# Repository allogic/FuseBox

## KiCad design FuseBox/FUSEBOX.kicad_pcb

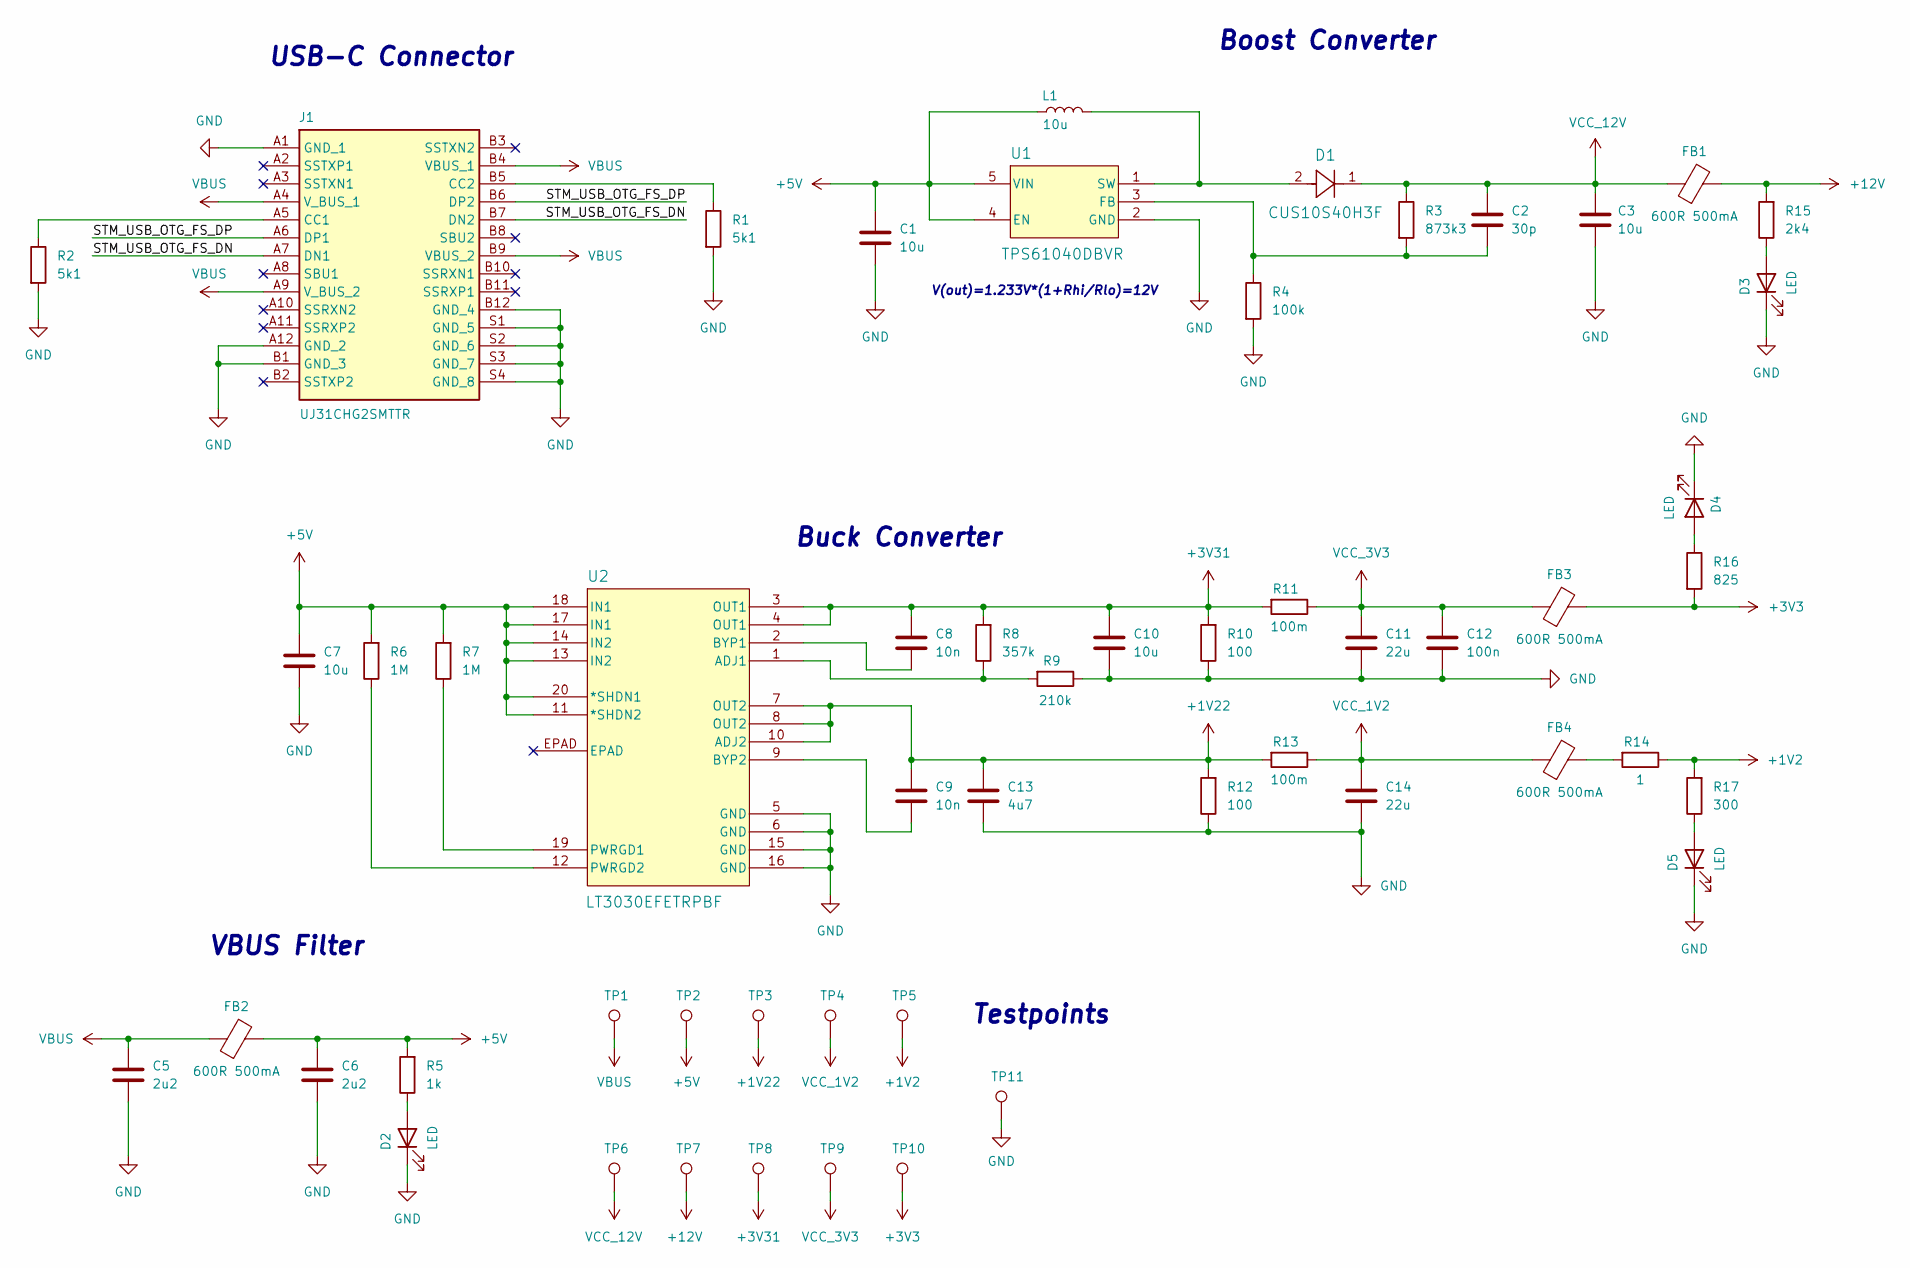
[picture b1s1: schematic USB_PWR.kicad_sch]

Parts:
C1, C3, C7, C10: 10u; C_0603_1608Metric_Pad1.08x0.95mm_HandSolder
C2: 30p; C_0603_1608Metric_Pad1.08x0.95mm_HandSolder
C5, C6: 2u2; C_0603_1608Metric_Pad1.08x0.95mm_HandSolder
C8, C9: 10n; C_0603_1608Metric_Pad1.08x0.95mm_HandSolder
C11, C14: 22u; C_0603_1608Metric_Pad1.08x0.95mm_HandSolder
C12: 100n; C_0603_1608Metric_Pad1.08x0.95mm_HandSolder
C13: 4u7; C_0603_1608Metric_Pad1.08x0.95mm_HandSolder
D1: CUS10S40H3F
D2, D3, D4, D5: LED; LED_0603_1608Metric
FB1, FB2, FB3, FB4: 600R 500mA; L_0603_1608Metric_Pad1.05x0.95mm_HandSolder
J1: UJ31CHG2SMTTR; Manufacturer_Part_Number UJ31-CH-G2-SMT-TR; Mouser Part Number 490-UJ31-CH-G2SMT-TR
L1: 10u; L_0603_1608Metric_Pad1.05x0.95mm_HandSolder
R1, R2: 5k1; R_0603_1608Metric_Pad0.98x0.95mm_HandSolder
R3: 873k3; R_0603_1608Metric_Pad0.98x0.95mm_HandSolder
R4: 100k; R_0603_1608Metric_Pad0.98x0.95mm_HandSolder
R5: 1k; R_0603_1608Metric_Pad0.98x0.95mm_HandSolder
R6, R7: 1M; R_0603_1608Metric_Pad0.98x0.95mm_HandSolder
R8: 357k; R_0603_1608Metric_Pad0.98x0.95mm_HandSolder
R9: 210k; R_0603_1608Metric_Pad0.98x0.95mm_HandSolder
R10, R12: 100; R_0603_1608Metric_Pad0.98x0.95mm_HandSolder
R11, R13: 100m; R_0603_1608Metric_Pad0.98x0.95mm_HandSolder
R14: 1; R_0603_1608Metric_Pad0.98x0.95mm_HandSolder
R15: 2k4; R_0603_1608Metric_Pad0.98x0.95mm_HandSolder
R16: 825; R_0603_1608Metric_Pad0.98x0.95mm_HandSolder
R17: 300; R_0603_1608Metric_Pad0.98x0.95mm_HandSolder
TP1, TP2, TP3, TP4, TP5, TP6, TP7, TP8, TP9, TP10, TP11: TestPoint; TestPoint_Pad_D3.0mm
U1: TPS61040DBVR
U2: LT3030EFETRPBF; LT8302ES8ETRPBF

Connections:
+1V2: R14.1, R17.2, TP5.1; also elsewhere on the board
+1V22: C9.1, C13.1, R12.2, R13.2, TP3.1, U2.7 (OUT2), U2.8 (OUT2), U2.10 (ADJ2)
+3V3: FB3.2, R16.2, TP10.1; also elsewhere on the board
+3V31: C8.1, C10.1, R8.2, R10.2, R11.2, TP8.1, U2.3 (OUT1), U2.4 (OUT1)
+5V: C1.1, C6.1, C7.1, FB2.2, L1.1, R5.2, R6.2, R7.2, TP2.1, U1.4 (EN), U1.5 (VIN), U2.11 (*SHDN2), U2.13 (IN2), U2.14 (IN2), U2.17 (IN1), U2.18 (IN1), U2.20 (*SHDN1)
+12V: FB1.2, R15.2, TP7.1
/USB_PWR/STM_USB_OTG_FS_DN: J1.A7 (DN1), J1.B7 (DN2)
/USB_PWR/STM_USB_OTG_FS_DP: J1.A6 (DP1), J1.B6 (DP2)
GND: C1.2, C3.2, C5.2, C6.2, C7.2, C10.2, C11.2, C12.2, C13.2, C14.2, D2.1 (K), D3.1 (K), D4.1 (K), D5.1 (K), J1.A1 (GND_1), J1.A12 (GND_2), J1.B1 (GND_3), J1.B12 (GND_4), J1.S1 (GND_5), J1.S2 (GND_6), J1.S3 (GND_7), J1.S4 (GND_8), R1.2, R2.2, R4.2, R9.1, R10.1, R12.1, TP11.1, U1.2 (GND), U2.5 (GND), U2.6 (GND), U2.15 (GND), U2.16 (GND); also elsewhere on the board
unnamed: D2.2 (A), R5.1
unnamed: D3.2 (A), R15.1
unnamed: D4.2 (A), R16.1
unnamed: D5.2 (A), R17.1
unnamed: FB4.2, R14.2
unnamed: J1.A5 (CC1), R2.1
unnamed: J1.B5 (CC2), R1.1
unnamed: C2.2, R3.2, R4.1, U1.3 (FB)
unnamed: D1.2, L1.2, U1.1 (SW)
unnamed: R8.1, R9.2, U2.1 (ADJ1)
unnamed: C8.2, U2.2 (BYP1)
unnamed: C9.2, U2.9 (BYP2)
unnamed: R7.1, U2.19 (PWRGD1)
unnamed: R6.1, U2.12 (PWRGD2)
VBUS: C5.1, FB2.1, J1.A4 (V_BUS_1), J1.A9 (V_BUS_2), J1.B4 (VBUS_1), J1.B9 (VBUS_2), TP1.1
VCC_1V2: C14.1, FB4.1, R13.1, TP4.1
VCC_3V3: C11.1, C12.1, FB3.1, R11.1, TP9.1
VCC_12V: C2.1, C3.1, D1.1, FB1.1, R3.1, TP6.1

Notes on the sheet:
Boost Converter
VBUS Filter
Buck Converter
V(out)=1.233V*(1+Rhi/Rlo)=12V
USB-C Connector
Testpoints

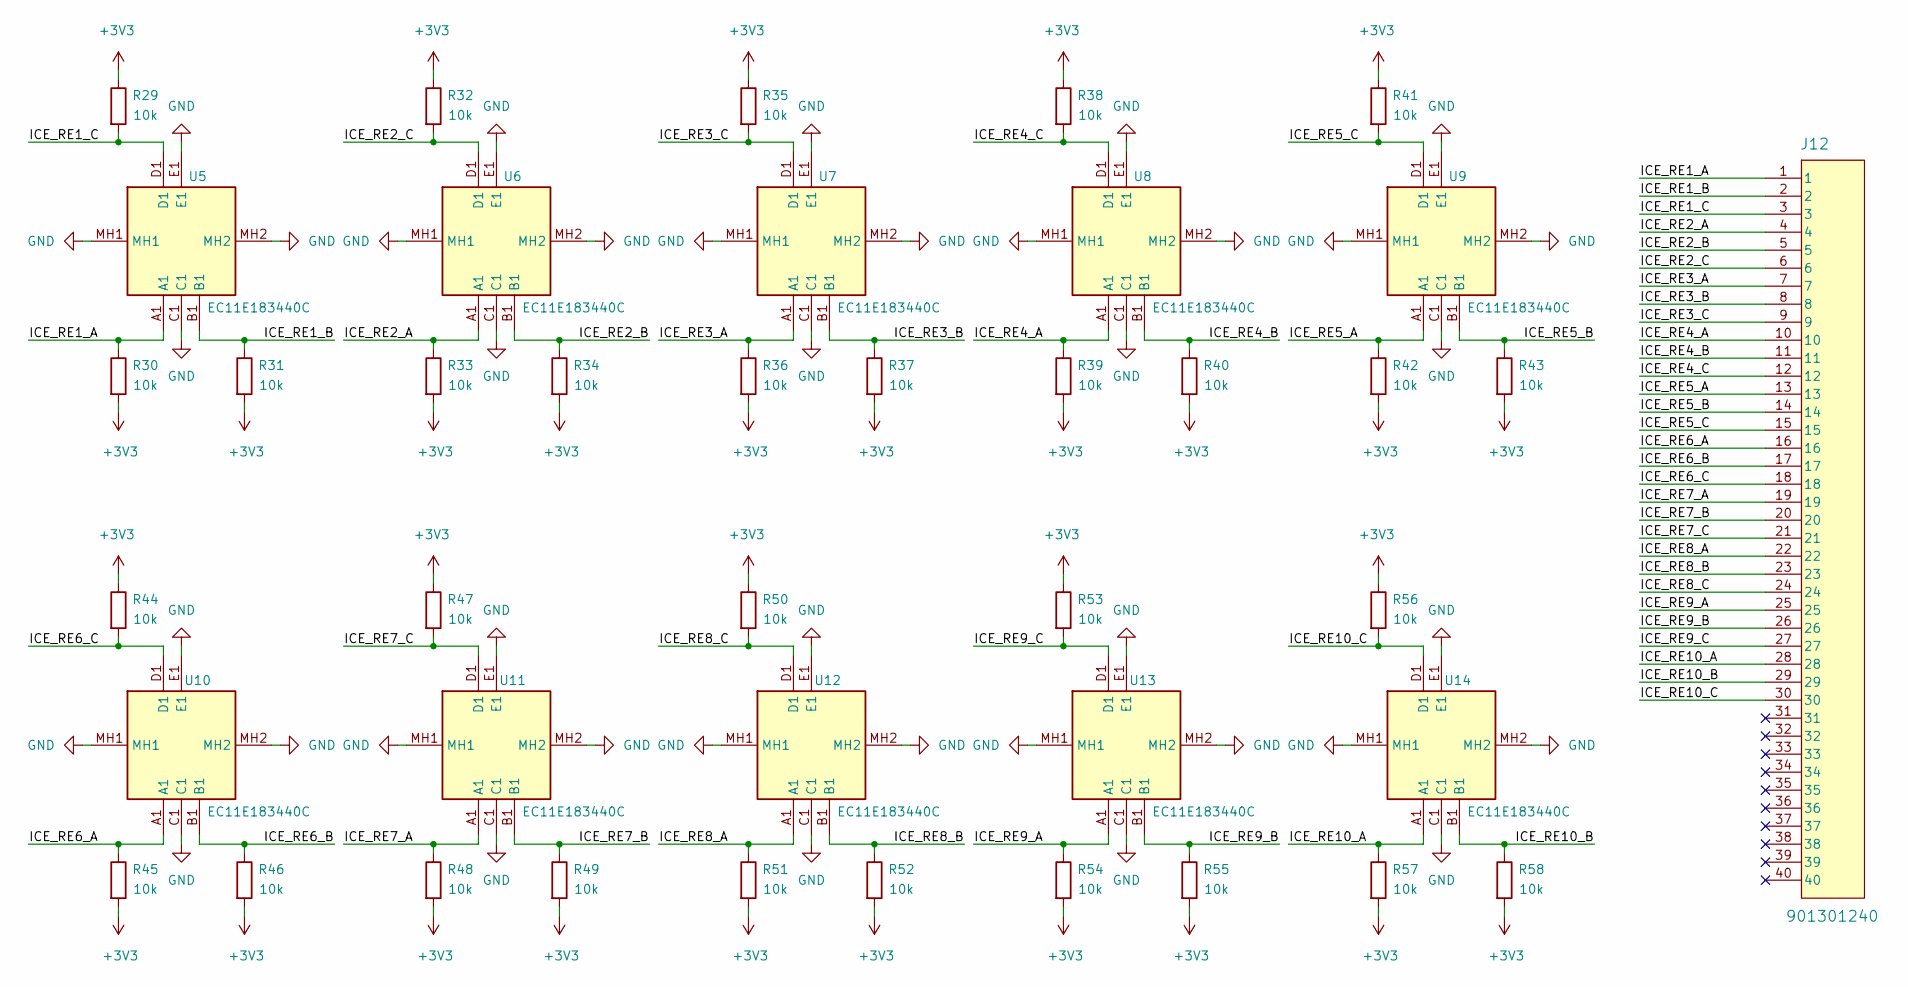
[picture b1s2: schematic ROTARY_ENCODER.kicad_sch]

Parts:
J12: 901301240
R29, R30, R31, R32, R33, R34, R35, R36, R37, R38, R39, R40, R41, R42, R43, R44, R45, R46, R47, R48, R49, R50, R51, R52, R53, R54, R55, R56, R57, R58: 10k; R_0603_1608Metric_Pad0.98x0.95mm_HandSolder
U5, U6, U7, U8, U9, U10, U11, U12, U13, U14: EC11E183440C; Manufacturer_Part_Number EC11E183440C; Mouser Part Number 688-EC11E183440C

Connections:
+3V3: R29.1, R30.2, R31.2, R32.1, R33.2, R34.2, R35.1, R36.2, R37.2, R38.1, R39.2, R40.2, R41.1, R42.2, R43.2, R44.1, R45.2, R46.2, R47.1, R48.2, R49.2, R50.1, R51.2, R52.2, R53.1, R54.2, R55.2, R56.1, R57.2, R58.2; also elsewhere on the board
/ROTARY_ENCODER/ICE_RE1_A: J12.1, R30.1, U5.A1
/ROTARY_ENCODER/ICE_RE1_B: J12.2, R31.1, U5.B1
/ROTARY_ENCODER/ICE_RE1_C: J12.3, R29.2, U5.D1
/ROTARY_ENCODER/ICE_RE2_A: J12.4, R33.1, U6.A1
/ROTARY_ENCODER/ICE_RE2_B: J12.5, R34.1, U6.B1
/ROTARY_ENCODER/ICE_RE2_C: J12.6, R32.2, U6.D1
/ROTARY_ENCODER/ICE_RE3_A: J12.7, R36.1, U7.A1
/ROTARY_ENCODER/ICE_RE3_B: J12.8, R37.1, U7.B1
/ROTARY_ENCODER/ICE_RE3_C: J12.9, R35.2, U7.D1
/ROTARY_ENCODER/ICE_RE4_A: J12.10, R39.1, U8.A1
/ROTARY_ENCODER/ICE_RE4_B: J12.11, R40.1, U8.B1
/ROTARY_ENCODER/ICE_RE4_C: J12.12, R38.2, U8.D1
/ROTARY_ENCODER/ICE_RE5_A: J12.13, R42.1, U9.A1
/ROTARY_ENCODER/ICE_RE5_B: J12.14, R43.1, U9.B1
/ROTARY_ENCODER/ICE_RE5_C: J12.15, R41.2, U9.D1
/ROTARY_ENCODER/ICE_RE6_A: J12.16, R45.1, U10.A1
/ROTARY_ENCODER/ICE_RE6_B: J12.17, R46.1, U10.B1
/ROTARY_ENCODER/ICE_RE6_C: J12.18, R44.2, U10.D1
/ROTARY_ENCODER/ICE_RE7_A: J12.19, R48.1, U11.A1
/ROTARY_ENCODER/ICE_RE7_B: J12.20, R49.1, U11.B1
/ROTARY_ENCODER/ICE_RE7_C: J12.21, R47.2, U11.D1
/ROTARY_ENCODER/ICE_RE8_A: J12.22, R51.1, U12.A1
/ROTARY_ENCODER/ICE_RE8_B: J12.23, R52.1, U12.B1
/ROTARY_ENCODER/ICE_RE8_C: J12.24, R50.2, U12.D1
/ROTARY_ENCODER/ICE_RE9_A: J12.25, R54.1, U13.A1
/ROTARY_ENCODER/ICE_RE9_B: J12.26, R55.1, U13.B1
/ROTARY_ENCODER/ICE_RE9_C: J12.27, R53.2, U13.D1
/ROTARY_ENCODER/ICE_RE10_A: J12.28, R57.1, U14.A1
/ROTARY_ENCODER/ICE_RE10_B: J12.29, R58.1, U14.B1
/ROTARY_ENCODER/ICE_RE10_C: J12.30, R56.2, U14.D1
GND: U5.C1, U5.E1, U5.MH1, U5.MH2, U6.C1, U6.E1, U6.MH1, U6.MH2, U7.C1, U7.E1, U7.MH1, U7.MH2, U8.C1, U8.E1, U8.MH1, U8.MH2, U9.C1, U9.E1, U9.MH1, U9.MH2, U10.C1, U10.E1, U10.MH1, U10.MH2, U11.C1, U11.E1, U11.MH1, U11.MH2, U12.C1, U12.E1, U12.MH1, U12.MH2, U13.C1, U13.E1, U13.MH1, U13.MH2, U14.C1, U14.E1, U14.MH1, U14.MH2; also elsewhere on the board

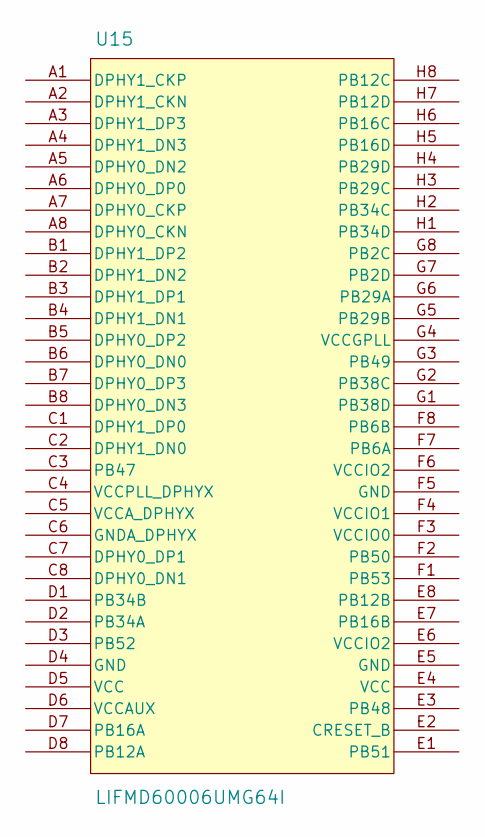
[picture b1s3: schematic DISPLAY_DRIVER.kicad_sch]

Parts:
U15: LIFMD60006UMG64I

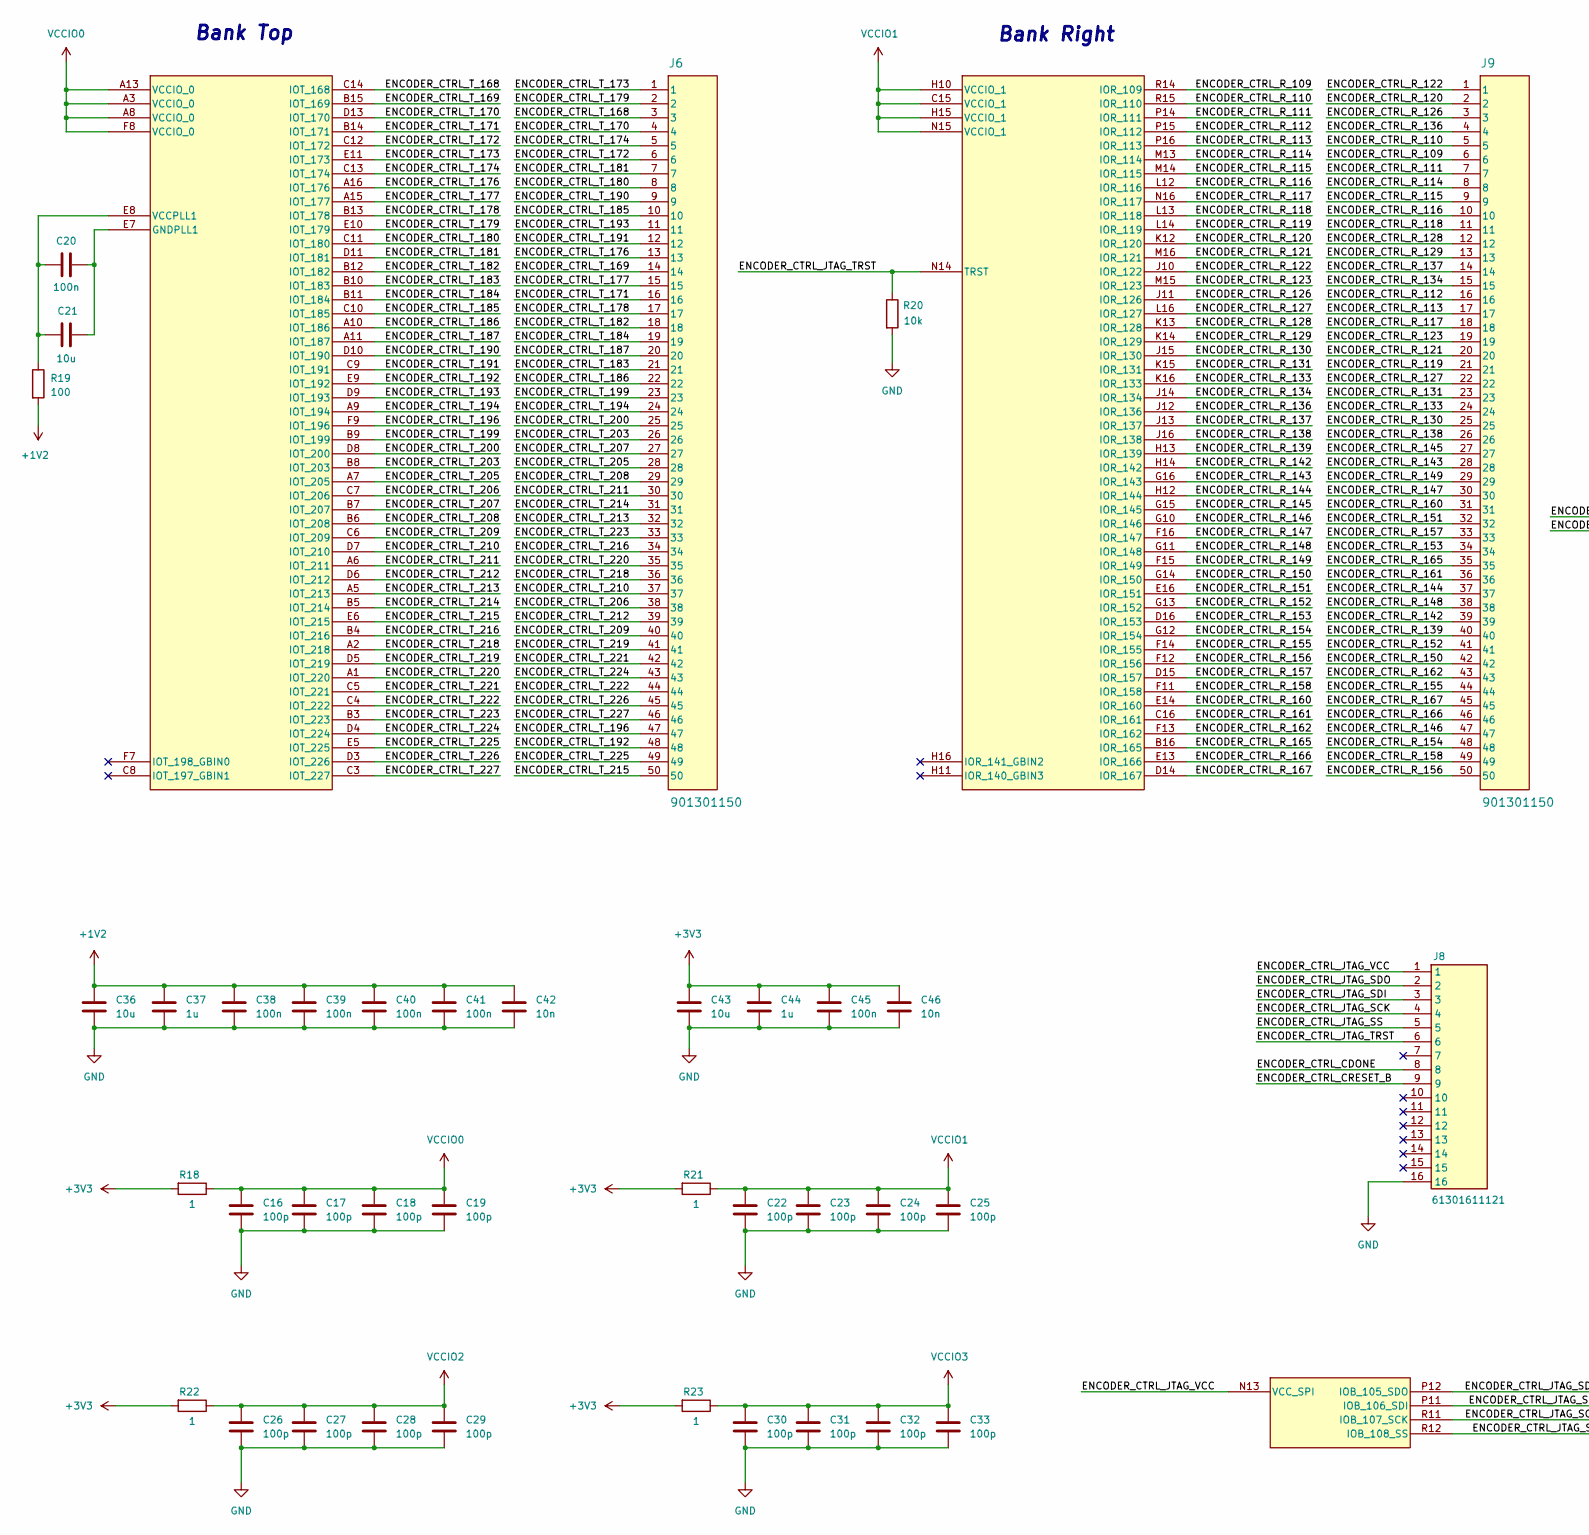
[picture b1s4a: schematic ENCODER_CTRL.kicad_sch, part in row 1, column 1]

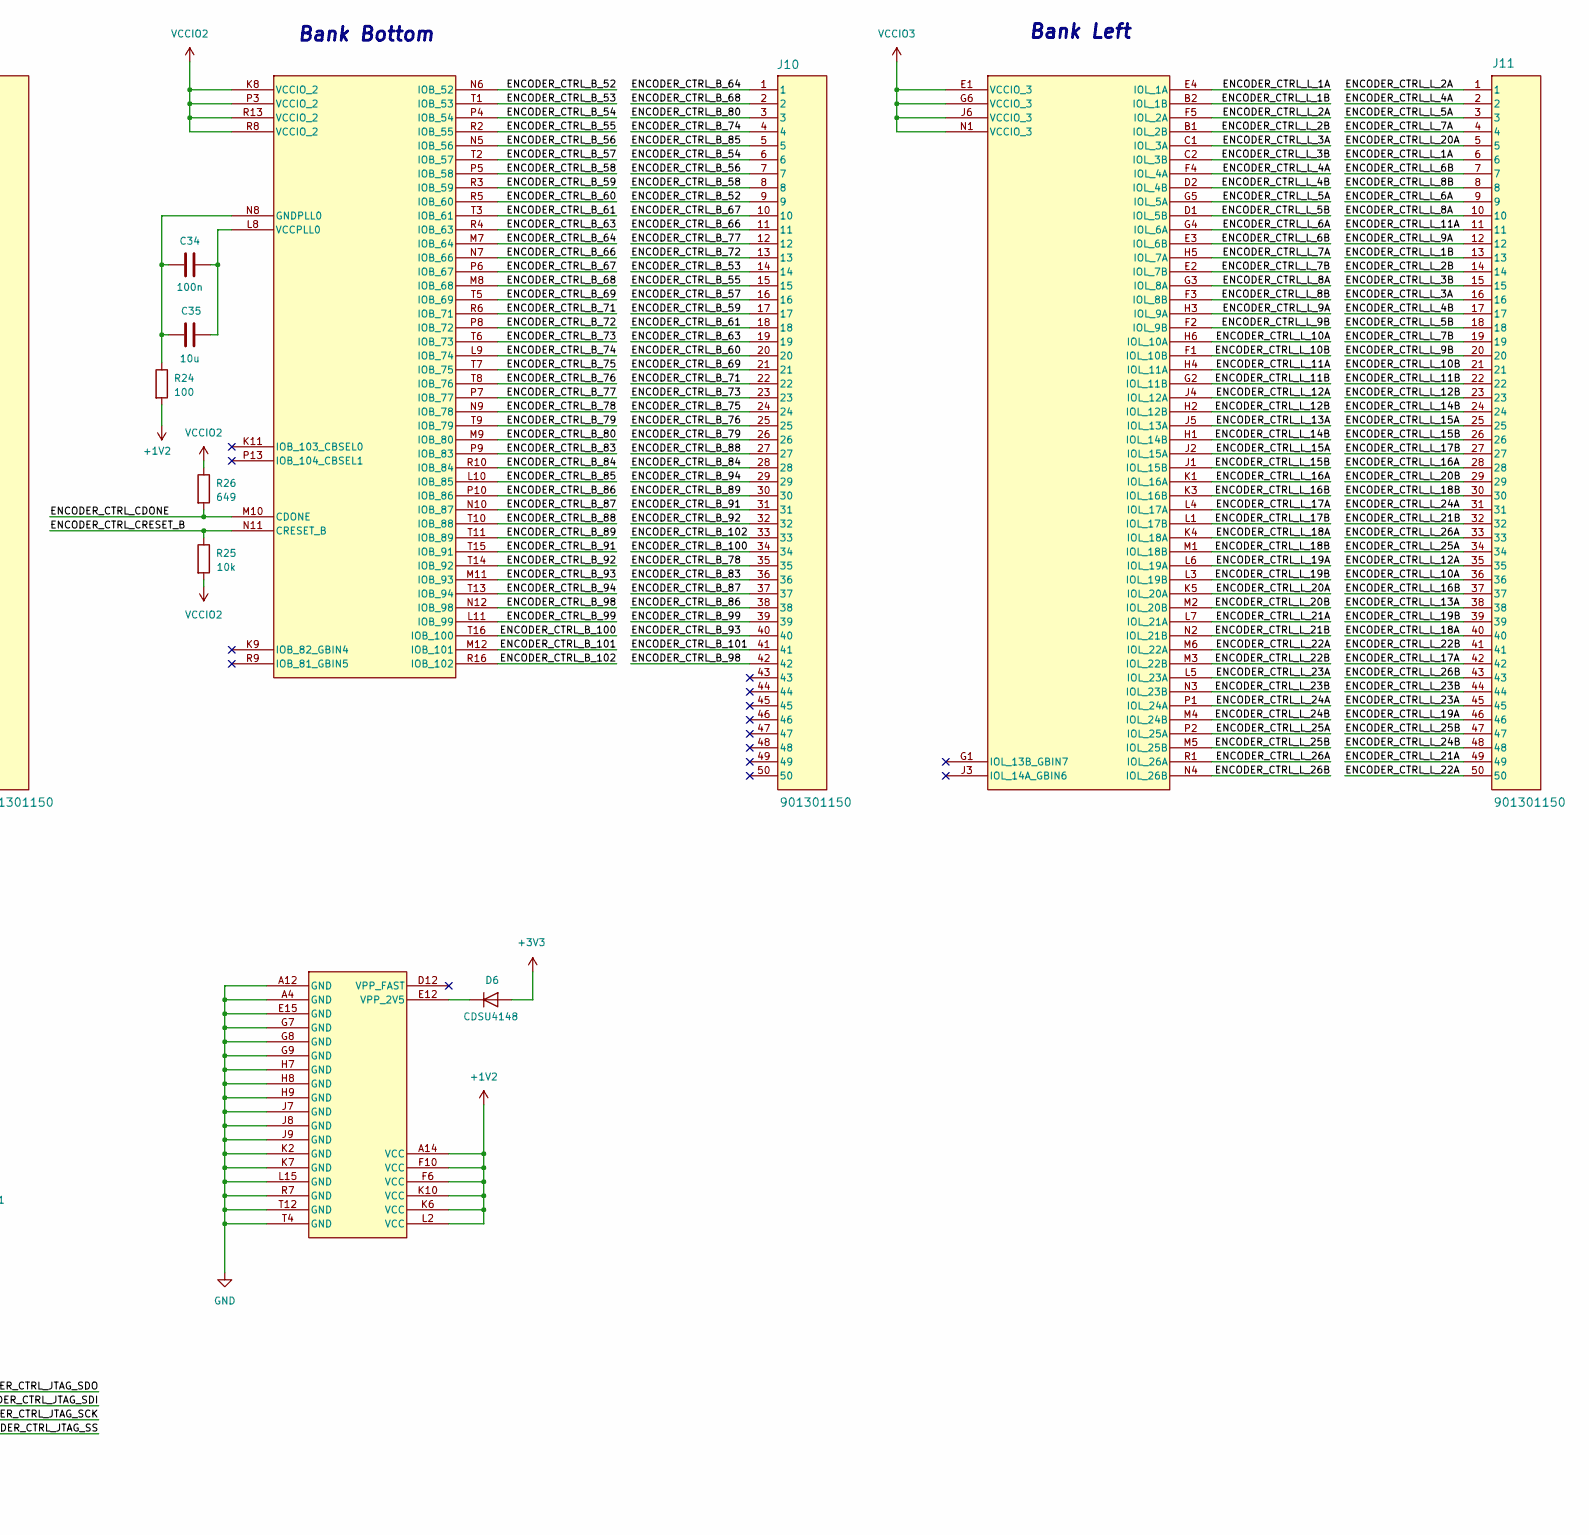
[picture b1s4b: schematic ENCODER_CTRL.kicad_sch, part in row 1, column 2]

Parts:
C16, C17, C18, C19, C22, C23, C24, C25, C26, C27, C28, C29, C30, C31, C32, C33: 100p; C_0603_1608Metric_Pad1.08x0.95mm_HandSolder
C20, C34, C38, C39, C40, C41, C45: 100n; C_0603_1608Metric_Pad1.08x0.95mm_HandSolder
C21, C35, C36, C43: 10u; C_0603_1608Metric_Pad1.08x0.95mm_HandSolder
C37, C44: 1u; C_0603_1608Metric_Pad1.08x0.95mm_HandSolder
C42, C46: 10n; C_0603_1608Metric_Pad1.08x0.95mm_HandSolder
D6: CDSU4148; D_0603_1608Metric_Pad1.05x0.95mm_HandSolder
J6, J9, J10, J11: 901301150
J8: 61301611121; Manufacturer_Part_Number 61301611121; Mouser Part Number 710-61301611121
R18, R21, R22, R23: 1; R_0603_1608Metric_Pad0.98x0.95mm_HandSolder
R19, R24: 100; R_0603_1608Metric_Pad0.98x0.95mm_HandSolder
R20, R25: 10k; R_0603_1608Metric_Pad0.98x0.95mm_HandSolder
R26: 649; R_0603_1608Metric_Pad0.98x0.95mm_HandSolder
U4: ICE40HX8KCT256

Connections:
+1V2: C36.1, C37.1, C38.1, C39.1, C40.1, C41.1, C42.1, R19.2, R24.2, U4.A14 (VCC), U4.F6 (VCC), U4.F10 (VCC), U4.K6 (VCC), U4.K10 (VCC), U4.L2 (VCC); also elsewhere on the board
+3V3: C43.1, C44.1, C45.1, C46.1, D6.2 (A), R18.2, R21.2, R22.2, R23.2; also elsewhere on the board
/ENCODER_CTRL/ENCODER_CTRL_B_52: J10.9, U4.N6 (IOB_52)
/ENCODER_CTRL/ENCODER_CTRL_B_53: J10.14, U4.T1 (IOB_53)
/ENCODER_CTRL/ENCODER_CTRL_B_54: J10.6, U4.P4 (IOB_54)
/ENCODER_CTRL/ENCODER_CTRL_B_55: J10.15, U4.R2 (IOB_55)
/ENCODER_CTRL/ENCODER_CTRL_B_56: J10.7, U4.N5 (IOB_56)
/ENCODER_CTRL/ENCODER_CTRL_B_57: J10.16, U4.T2 (IOB_57)
/ENCODER_CTRL/ENCODER_CTRL_B_58: J10.8, U4.P5 (IOB_58)
/ENCODER_CTRL/ENCODER_CTRL_B_59: J10.17, U4.R3 (IOB_59)
/ENCODER_CTRL/ENCODER_CTRL_B_60: J10.20, U4.R5 (IOB_60)
/ENCODER_CTRL/ENCODER_CTRL_B_61: J10.18, U4.T3 (IOB_61)
/ENCODER_CTRL/ENCODER_CTRL_B_63: J10.19, U4.R4 (IOB_63)
/ENCODER_CTRL/ENCODER_CTRL_B_64: J10.1, U4.M7 (IOB_64)
/ENCODER_CTRL/ENCODER_CTRL_B_66: J10.11, U4.N7 (IOB_66)
/ENCODER_CTRL/ENCODER_CTRL_B_67: J10.10, U4.P6 (IOB_67)
/ENCODER_CTRL/ENCODER_CTRL_B_68: J10.2, U4.M8 (IOB_68)
/ENCODER_CTRL/ENCODER_CTRL_B_69: J10.21, U4.T5 (IOB_69)
/ENCODER_CTRL/ENCODER_CTRL_B_71: J10.22, U4.R6 (IOB_71)
/ENCODER_CTRL/ENCODER_CTRL_B_72: J10.13, U4.P8 (IOB_72)
/ENCODER_CTRL/ENCODER_CTRL_B_73: J10.23, U4.T6 (IOB_73)
/ENCODER_CTRL/ENCODER_CTRL_B_74: J10.4, U4.L9 (IOB_74)
/ENCODER_CTRL/ENCODER_CTRL_B_75: J10.24, U4.T7 (IOB_75)
/ENCODER_CTRL/ENCODER_CTRL_B_76: J10.25, U4.T8 (IOB_76)
/ENCODER_CTRL/ENCODER_CTRL_B_77: J10.12, U4.P7 (IOB_77)
/ENCODER_CTRL/ENCODER_CTRL_B_78: J10.35, U4.N9 (IOB_78)
/ENCODER_CTRL/ENCODER_CTRL_B_79: J10.26, U4.T9 (IOB_79)
/ENCODER_CTRL/ENCODER_CTRL_B_80: J10.3, U4.M9 (IOB_80)
/ENCODER_CTRL/ENCODER_CTRL_B_83: J10.36, U4.P9 (IOB_83)
/ENCODER_CTRL/ENCODER_CTRL_B_84: J10.28, U4.R10 (IOB_84)
/ENCODER_CTRL/ENCODER_CTRL_B_85: J10.5, U4.L10 (IOB_85)
/ENCODER_CTRL/ENCODER_CTRL_B_86: J10.38, U4.P10 (IOB_86)
/ENCODER_CTRL/ENCODER_CTRL_B_87: J10.37, U4.N10 (IOB_87)
/ENCODER_CTRL/ENCODER_CTRL_B_88: J10.27, U4.T10 (IOB_88)
/ENCODER_CTRL/ENCODER_CTRL_B_89: J10.30, U4.T11 (IOB_89)
/ENCODER_CTRL/ENCODER_CTRL_B_91: J10.31, U4.T15 (IOB_91)
/ENCODER_CTRL/ENCODER_CTRL_B_92: J10.32, U4.T14 (IOB_92)
/ENCODER_CTRL/ENCODER_CTRL_B_93: J10.40, U4.M11 (IOB_93)
/ENCODER_CTRL/ENCODER_CTRL_B_94: J10.29, U4.T13 (IOB_94)
/ENCODER_CTRL/ENCODER_CTRL_B_98: J10.42, U4.N12 (IOB_98)
/ENCODER_CTRL/ENCODER_CTRL_B_99: J10.39, U4.L11 (IOB_99)
/ENCODER_CTRL/ENCODER_CTRL_B_100: J10.34, U4.T16 (IOB_100)
/ENCODER_CTRL/ENCODER_CTRL_B_101: J10.41, U4.M12 (IOB_101)
/ENCODER_CTRL/ENCODER_CTRL_B_102: J10.33, U4.R16 (IOB_102)
/ENCODER_CTRL/ENCODER_CTRL_CDONE: J8.8, R26.2, U4.M10 (CDONE)
/ENCODER_CTRL/ENCODER_CTRL_CRESET_B: J8.9, R25.1, U4.N11 (CRESET_B)
/ENCODER_CTRL/ENCODER_CTRL_JTAG_SCK: J8.4, U4.R11 (IOB_107_SCK)
/ENCODER_CTRL/ENCODER_CTRL_JTAG_SDI: J8.3, U4.P11 (IOB_106_SDI)
/ENCODER_CTRL/ENCODER_CTRL_JTAG_SDO: J8.2, U4.P12 (IOB_105_SDO)
/ENCODER_CTRL/ENCODER_CTRL_JTAG_SS: J8.5, U4.R12 (IOB_108_SS)
/ENCODER_CTRL/ENCODER_CTRL_JTAG_TRST: J8.6, R20.1, U4.N14 (TRST)
/ENCODER_CTRL/ENCODER_CTRL_JTAG_VCC: J8.1, U4.N13 (VCC_SPI)
/ENCODER_CTRL/ENCODER_CTRL_L_1A: J11.6, U4.E4 (IOL_1A)
/ENCODER_CTRL/ENCODER_CTRL_L_1B: J11.13, U4.B2 (IOL_1B)
/ENCODER_CTRL/ENCODER_CTRL_L_2A: J11.1, U4.F5 (IOL_2A)
/ENCODER_CTRL/ENCODER_CTRL_L_2B: J11.14, U4.B1 (IOL_2B)
/ENCODER_CTRL/ENCODER_CTRL_L_3A: J11.16, U4.C1 (IOL_3A)
/ENCODER_CTRL/ENCODER_CTRL_L_3B: J11.15, U4.C2 (IOL_3B)
/ENCODER_CTRL/ENCODER_CTRL_L_4A: J11.2, U4.F4 (IOL_4A)
/ENCODER_CTRL/ENCODER_CTRL_L_4B: J11.17, U4.D2 (IOL_4B)
/ENCODER_CTRL/ENCODER_CTRL_L_5A: J11.3, U4.G5 (IOL_5A)
/ENCODER_CTRL/ENCODER_CTRL_L_5B: J11.18, U4.D1 (IOL_5B)
/ENCODER_CTRL/ENCODER_CTRL_L_6A: J11.9, U4.G4 (IOL_6A)
/ENCODER_CTRL/ENCODER_CTRL_L_6B: J11.7, U4.E3 (IOL_6B)
/ENCODER_CTRL/ENCODER_CTRL_L_7A: J11.4, U4.H5 (IOL_7A)
/ENCODER_CTRL/ENCODER_CTRL_L_7B: J11.19, U4.E2 (IOL_7B)
/ENCODER_CTRL/ENCODER_CTRL_L_8A: J11.10, U4.G3 (IOL_8A)
/ENCODER_CTRL/ENCODER_CTRL_L_8B: J11.8, U4.F3 (IOL_8B)
/ENCODER_CTRL/ENCODER_CTRL_L_9A: J11.12, U4.H3 (IOL_9A)
/ENCODER_CTRL/ENCODER_CTRL_L_9B: J11.20, U4.F2 (IOL_9B)
/ENCODER_CTRL/ENCODER_CTRL_L_10A: J11.36, U4.H6 (IOL_10A)
/ENCODER_CTRL/ENCODER_CTRL_L_10B: J11.21, U4.F1 (IOL_10B)
/ENCODER_CTRL/ENCODER_CTRL_L_11A: J11.11, U4.H4 (IOL_11A)
/ENCODER_CTRL/ENCODER_CTRL_L_11B: J11.22, U4.G2 (IOL_11B)
/ENCODER_CTRL/ENCODER_CTRL_L_12A: J11.35, U4.J4 (IOL_12A)
/ENCODER_CTRL/ENCODER_CTRL_L_12B: J11.23, U4.H2 (IOL_12B)
/ENCODER_CTRL/ENCODER_CTRL_L_13A: J11.38, U4.J5 (IOL_13A)
/ENCODER_CTRL/ENCODER_CTRL_L_14B: J11.24, U4.H1 (IOL_14B)
/ENCODER_CTRL/ENCODER_CTRL_L_15A: J11.25, U4.J2 (IOL_15A)
/ENCODER_CTRL/ENCODER_CTRL_L_15B: J11.26, U4.J1 (IOL_15B)
/ENCODER_CTRL/ENCODER_CTRL_L_16A: J11.28, U4.K1 (IOL_16A)
/ENCODER_CTRL/ENCODER_CTRL_L_16B: J11.37, U4.K3 (IOL_16B)
/ENCODER_CTRL/ENCODER_CTRL_L_17A: J11.42, U4.L4 (IOL_17A)
/ENCODER_CTRL/ENCODER_CTRL_L_17B: J11.27, U4.L1 (IOL_17B)
/ENCODER_CTRL/ENCODER_CTRL_L_18A: J11.40, U4.K4 (IOL_18A)
/ENCODER_CTRL/ENCODER_CTRL_L_18B: J11.30, U4.M1 (IOL_18B)
/ENCODER_CTRL/ENCODER_CTRL_L_19A: J11.46, U4.L6 (IOL_19A)
/ENCODER_CTRL/ENCODER_CTRL_L_19B: J11.39, U4.L3 (IOL_19B)
/ENCODER_CTRL/ENCODER_CTRL_L_20A: J11.5, U4.K5 (IOL_20A)
/ENCODER_CTRL/ENCODER_CTRL_L_20B: J11.29, U4.M2 (IOL_20B)
/ENCODER_CTRL/ENCODER_CTRL_L_21A: J11.49, U4.L7 (IOL_21A)
/ENCODER_CTRL/ENCODER_CTRL_L_21B: J11.32, U4.N2 (IOL_21B)
/ENCODER_CTRL/ENCODER_CTRL_L_22A: J11.50, U4.M6 (IOL_22A)
/ENCODER_CTRL/ENCODER_CTRL_L_22B: J11.41, U4.M3 (IOL_22B)
/ENCODER_CTRL/ENCODER_CTRL_L_23A: J11.45, U4.L5 (IOL_23A)
/ENCODER_CTRL/ENCODER_CTRL_L_23B: J11.44, U4.N3 (IOL_23B)
/ENCODER_CTRL/ENCODER_CTRL_L_24A: J11.31, U4.P1 (IOL_24A)
/ENCODER_CTRL/ENCODER_CTRL_L_24B: J11.48, U4.M4 (IOL_24B)
/ENCODER_CTRL/ENCODER_CTRL_L_25A: J11.34, U4.P2 (IOL_25A)
/ENCODER_CTRL/ENCODER_CTRL_L_25B: J11.47, U4.M5 (IOL_25B)
/ENCODER_CTRL/ENCODER_CTRL_L_26A: J11.33, U4.R1 (IOL_26A)
/ENCODER_CTRL/ENCODER_CTRL_L_26B: J11.43, U4.N4 (IOL_26B)
/ENCODER_CTRL/ENCODER_CTRL_R_109: J9.6, U4.R14 (IOR_109)
/ENCODER_CTRL/ENCODER_CTRL_R_110: J9.5, U4.R15 (IOR_110)
/ENCODER_CTRL/ENCODER_CTRL_R_111: J9.7, U4.P14 (IOR_111)
/ENCODER_CTRL/ENCODER_CTRL_R_112: J9.16, U4.P15 (IOR_112)
/ENCODER_CTRL/ENCODER_CTRL_R_113: J9.17, U4.P16 (IOR_113)
/ENCODER_CTRL/ENCODER_CTRL_R_114: J9.8, U4.M13 (IOR_114)
/ENCODER_CTRL/ENCODER_CTRL_R_115: J9.9, U4.M14 (IOR_115)
/ENCODER_CTRL/ENCODER_CTRL_R_116: J9.10, U4.L12 (IOR_116)
/ENCODER_CTRL/ENCODER_CTRL_R_117: J9.18, U4.N16 (IOR_117)
/ENCODER_CTRL/ENCODER_CTRL_R_118: J9.11, U4.L13 (IOR_118)
/ENCODER_CTRL/ENCODER_CTRL_R_119: J9.21, U4.L14 (IOR_119)
/ENCODER_CTRL/ENCODER_CTRL_R_120: J9.2, U4.K12 (IOR_120)
/ENCODER_CTRL/ENCODER_CTRL_R_121: J9.20, U4.M16 (IOR_121)
/ENCODER_CTRL/ENCODER_CTRL_R_122: J9.1, U4.J10 (IOR_122)
/ENCODER_CTRL/ENCODER_CTRL_R_123: J9.19, U4.M15 (IOR_123)
/ENCODER_CTRL/ENCODER_CTRL_R_126: J9.3, U4.J11 (IOR_126)
/ENCODER_CTRL/ENCODER_CTRL_R_127: J9.22, U4.L16 (IOR_127)
/ENCODER_CTRL/ENCODER_CTRL_R_128: J9.12, U4.K13 (IOR_128)
/ENCODER_CTRL/ENCODER_CTRL_R_129: J9.13, U4.K14 (IOR_129)
/ENCODER_CTRL/ENCODER_CTRL_R_130: J9.25, U4.J15 (IOR_130)
/ENCODER_CTRL/ENCODER_CTRL_R_131: J9.23, U4.K15 (IOR_131)
/ENCODER_CTRL/ENCODER_CTRL_R_133: J9.24, U4.K16 (IOR_133)
/ENCODER_CTRL/ENCODER_CTRL_R_134: J9.15, U4.J14 (IOR_134)
/ENCODER_CTRL/ENCODER_CTRL_R_136: J9.4, U4.J12 (IOR_136)
/ENCODER_CTRL/ENCODER_CTRL_R_137: J9.14, U4.J13 (IOR_137)
/ENCODER_CTRL/ENCODER_CTRL_R_138: J9.26, U4.J16 (IOR_138)
/ENCODER_CTRL/ENCODER_CTRL_R_139: J9.40, U4.H13 (IOR_139)
/ENCODER_CTRL/ENCODER_CTRL_R_142: J9.39, U4.H14 (IOR_142)
/ENCODER_CTRL/ENCODER_CTRL_R_143: J9.28, U4.G16 (IOR_143)
/ENCODER_CTRL/ENCODER_CTRL_R_144: J9.37, U4.H12 (IOR_144)
/ENCODER_CTRL/ENCODER_CTRL_R_145: J9.27, U4.G15 (IOR_145)
/ENCODER_CTRL/ENCODER_CTRL_R_146: J9.47, U4.G10 (IOR_146)
/ENCODER_CTRL/ENCODER_CTRL_R_147: J9.30, U4.F16 (IOR_147)
/ENCODER_CTRL/ENCODER_CTRL_R_148: J9.38, U4.G11 (IOR_148)
/ENCODER_CTRL/ENCODER_CTRL_R_149: J9.29, U4.F15 (IOR_149)
/ENCODER_CTRL/ENCODER_CTRL_R_150: J9.42, U4.G14 (IOR_150)
/ENCODER_CTRL/ENCODER_CTRL_R_151: J9.32, U4.E16 (IOR_151)
/ENCODER_CTRL/ENCODER_CTRL_R_152: J9.41, U4.G13 (IOR_152)
/ENCODER_CTRL/ENCODER_CTRL_R_153: J9.34, U4.D16 (IOR_153)
/ENCODER_CTRL/ENCODER_CTRL_R_154: J9.48, U4.G12 (IOR_154)
/ENCODER_CTRL/ENCODER_CTRL_R_155: J9.44, U4.F14 (IOR_155)
/ENCODER_CTRL/ENCODER_CTRL_R_156: J9.50, U4.F12 (IOR_156)
/ENCODER_CTRL/ENCODER_CTRL_R_157: J9.33, U4.D15 (IOR_157)
/ENCODER_CTRL/ENCODER_CTRL_R_158: J9.49, U4.F11 (IOR_158)
/ENCODER_CTRL/ENCODER_CTRL_R_160: J9.31, U4.E14 (IOR_160)
/ENCODER_CTRL/ENCODER_CTRL_R_161: J9.36, U4.C16 (IOR_161)
/ENCODER_CTRL/ENCODER_CTRL_R_162: J9.43, U4.F13 (IOR_162)
/ENCODER_CTRL/ENCODER_CTRL_R_165: J9.35, U4.B16 (IOR_165)
/ENCODER_CTRL/ENCODER_CTRL_R_166: J9.46, U4.E13 (IOR_166)
/ENCODER_CTRL/ENCODER_CTRL_R_167: J9.45, U4.D14 (IOR_167)
/ENCODER_CTRL/ENCODER_CTRL_T_168: J6.3, U4.C14 (IOT_168)
/ENCODER_CTRL/ENCODER_CTRL_T_169: J6.14, U4.B15 (IOT_169)
/ENCODER_CTRL/ENCODER_CTRL_T_170: J6.4, U4.D13 (IOT_170)
/ENCODER_CTRL/ENCODER_CTRL_T_171: J6.16, U4.B14 (IOT_171)
/ENCODER_CTRL/ENCODER_CTRL_T_172: J6.6, U4.C12 (IOT_172)
/ENCODER_CTRL/ENCODER_CTRL_T_173: J6.1, U4.E11 (IOT_173)
/ENCODER_CTRL/ENCODER_CTRL_T_174: J6.5, U4.C13 (IOT_174)
/ENCODER_CTRL/ENCODER_CTRL_T_176: J6.13, U4.A16 (IOT_176)
/ENCODER_CTRL/ENCODER_CTRL_T_177: J6.15, U4.A15 (IOT_177)
/ENCODER_CTRL/ENCODER_CTRL_T_178: J6.17, U4.B13 (IOT_178)
/ENCODER_CTRL/ENCODER_CTRL_T_179: J6.2, U4.E10 (IOT_179)
/ENCODER_CTRL/ENCODER_CTRL_T_180: J6.8, U4.C11 (IOT_180)
/ENCODER_CTRL/ENCODER_CTRL_T_181: J6.7, U4.D11 (IOT_181)
/ENCODER_CTRL/ENCODER_CTRL_T_182: J6.18, U4.B12 (IOT_182)
/ENCODER_CTRL/ENCODER_CTRL_T_183: J6.21, U4.B10 (IOT_183)
/ENCODER_CTRL/ENCODER_CTRL_T_184: J6.19, U4.B11 (IOT_184)
/ENCODER_CTRL/ENCODER_CTRL_T_185: J6.10, U4.C10 (IOT_185)
/ENCODER_CTRL/ENCODER_CTRL_T_186: J6.22, U4.A10 (IOT_186)
/ENCODER_CTRL/ENCODER_CTRL_T_187: J6.20, U4.A11 (IOT_187)
/ENCODER_CTRL/ENCODER_CTRL_T_190: J6.9, U4.D10 (IOT_190)
/ENCODER_CTRL/ENCODER_CTRL_T_191: J6.12, U4.C9 (IOT_191)
/ENCODER_CTRL/ENCODER_CTRL_T_192: J6.48, U4.E9 (IOT_192)
/ENCODER_CTRL/ENCODER_CTRL_T_193: J6.11, U4.D9 (IOT_193)
/ENCODER_CTRL/ENCODER_CTRL_T_194: J6.24, U4.A9 (IOT_194)
/ENCODER_CTRL/ENCODER_CTRL_T_196: J6.47, U4.F9 (IOT_196)
/ENCODER_CTRL/ENCODER_CTRL_T_199: J6.23, U4.B9 (IOT_199)
/ENCODER_CTRL/ENCODER_CTRL_T_200: J6.25, U4.D8 (IOT_200)
/ENCODER_CTRL/ENCODER_CTRL_T_203: J6.26, U4.B8 (IOT_203)
/ENCODER_CTRL/ENCODER_CTRL_T_205: J6.28, U4.A7 (IOT_205)
/ENCODER_CTRL/ENCODER_CTRL_T_206: J6.38, U4.C7 (IOT_206)
/ENCODER_CTRL/ENCODER_CTRL_T_207: J6.27, U4.B7 (IOT_207)
/ENCODER_CTRL/ENCODER_CTRL_T_208: J6.29, U4.B6 (IOT_208)
/ENCODER_CTRL/ENCODER_CTRL_T_209: J6.40, U4.C6 (IOT_209)
/ENCODER_CTRL/ENCODER_CTRL_T_210: J6.37, U4.D7 (IOT_210)
/ENCODER_CTRL/ENCODER_CTRL_T_211: J6.30, U4.A6 (IOT_211)
/ENCODER_CTRL/ENCODER_CTRL_T_212: J6.39, U4.D6 (IOT_212)
/ENCODER_CTRL/ENCODER_CTRL_T_213: J6.32, U4.A5 (IOT_213)
/ENCODER_CTRL/ENCODER_CTRL_T_214: J6.31, U4.B5 (IOT_214)
/ENCODER_CTRL/ENCODER_CTRL_T_215: J6.50, U4.E6 (IOT_215)
/ENCODER_CTRL/ENCODER_CTRL_T_216: J6.34, U4.B4 (IOT_216)
/ENCODER_CTRL/ENCODER_CTRL_T_218: J6.36, U4.A2 (IOT_218)
/ENCODER_CTRL/ENCODER_CTRL_T_219: J6.41, U4.D5 (IOT_219)
/ENCODER_CTRL/ENCODER_CTRL_T_220: J6.35, U4.A1 (IOT_220)
/ENCODER_CTRL/ENCODER_CTRL_T_221: J6.42, U4.C5 (IOT_221)
/ENCODER_CTRL/ENCODER_CTRL_T_222: J6.44, U4.C4 (IOT_222)
/ENCODER_CTRL/ENCODER_CTRL_T_223: J6.33, U4.B3 (IOT_223)
/ENCODER_CTRL/ENCODER_CTRL_T_224: J6.43, U4.D4 (IOT_224)
/ENCODER_CTRL/ENCODER_CTRL_T_225: J6.49, U4.E5 (IOT_225)
/ENCODER_CTRL/ENCODER_CTRL_T_226: J6.45, U4.D3 (IOT_226)
/ENCODER_CTRL/ENCODER_CTRL_T_227: J6.46, U4.C3 (IOT_227)
GND: C16.2, C17.2, C18.2, C19.2, C22.2, C23.2, C24.2, C25.2, C26.2, C27.2, C28.2, C29.2, C30.2, C31.2, C32.2, C33.2, C36.2, C37.2, C38.2, C39.2, C40.2, C41.2, C42.2, C43.2, C44.2, C45.2, C46.2, J8.16, R20.2, U4.A4 (GND), U4.A12 (GND), U4.E15 (GND), U4.G7 (GND), U4.G8 (GND), U4.G9 (GND), U4.H7 (GND), U4.H8 (GND), U4.H9 (GND), U4.J7 (GND), U4.J8 (GND), U4.J9 (GND), U4.K2 (GND), U4.K7 (GND), U4.L15 (GND), U4.R7 (GND), U4.T4 (GND), U4.T12 (GND); also elsewhere on the board
unnamed: D6.1 (K), U4.E12 (VPP_2V5)
unnamed: C20.2, C21.2, U4.E7 (GNDPLL1)
unnamed: C20.1, C21.1, R19.1, U4.E8 (VCCPLL1)
unnamed: C34.1, C35.1, R24.1, U4.N8 (GNDPLL0)
unnamed: C34.2, C35.2, U4.L8 (VCCPLL0)
VCCIO0: C16.1, C17.1, C18.1, C19.1, R18.1, U4.A3 (VCCIO_0), U4.A8 (VCCIO_0), U4.A13 (VCCIO_0), U4.F8 (VCCIO_0)
VCCIO1: C22.1, C23.1, C24.1, C25.1, R21.1, U4.C15 (VCCIO_1), U4.H10 (VCCIO_1), U4.H15 (VCCIO_1), U4.N15 (VCCIO_1)
VCCIO2: C26.1, C27.1, C28.1, C29.1, R22.1, R25.2, R26.1, U4.K8 (VCCIO_2), U4.P3 (VCCIO_2), U4.R8 (VCCIO_2), U4.R13 (VCCIO_2)
VCCIO3: C30.1, C31.1, C32.1, C33.1, R23.1, U4.E1 (VCCIO_3), U4.G6 (VCCIO_3), U4.J6 (VCCIO_3), U4.N1 (VCCIO_3)

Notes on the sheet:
Bank Right
Bank Bottom
Bank Left
Bank Top
